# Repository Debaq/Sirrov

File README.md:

<hr>

Simulador interactivo de respuesta reflejo ovulo vestibular

Sirrov es un simulador del movimiento ocular y la respuesta vestibular frente a pruebas caloricas, movimientos rotacionales. El hardware esta basado en raspberri py pero es perfectamente utilizable en otras plataformas que admitan python, sdl, y la posibilidad de conectar dos pantallas spi, a continuación una descripción del equipo en cuestión:

Estructura del proyecto:
- Software [Software]
    - Sirrov 
    - Sirrov-ctrl
- Hardware [Hardware]
    - Eye Pi [eye-pi]
    - Eye Pressure [ ]
    - Ear Sensor [ ]
    - Neck Sensor [ ]
    - Power Supply [ ]
- Documentación [doc](doc/)
    - Imagenes usadas [img]

# Colaboradores
- Escuela de Tecnología Médica Universidad Austral de Chile (http://tmedicapm.uach.cl/)
- TM. Eliezer Lillo Oyarzo  (https://cl.linkedin.com/in/eliezer-neftal%C3%AD-lillo-oyarzo-90810089)

*Sirrov, es un proyecto creado por Nicolás Quezada Baier*

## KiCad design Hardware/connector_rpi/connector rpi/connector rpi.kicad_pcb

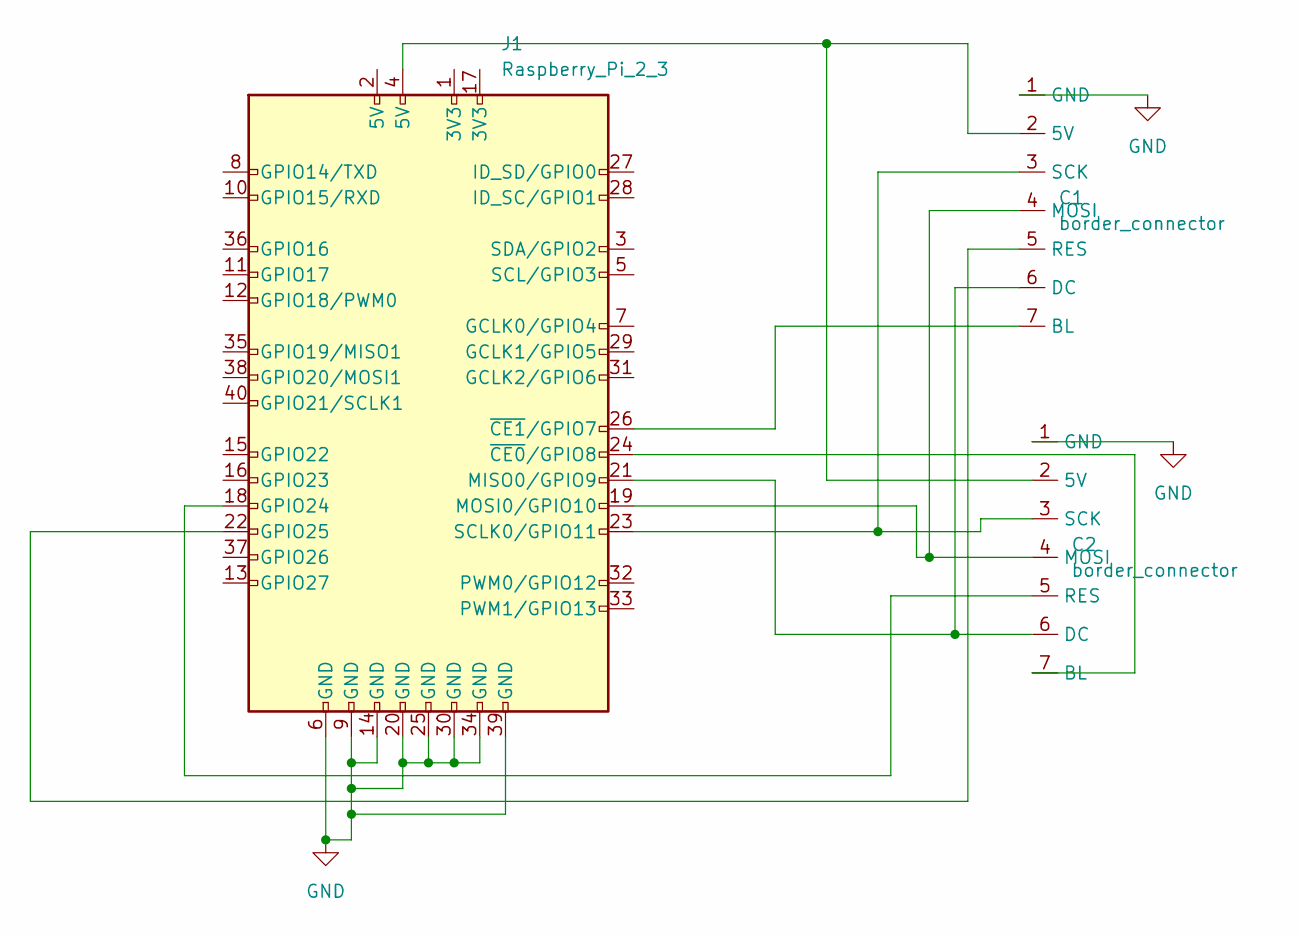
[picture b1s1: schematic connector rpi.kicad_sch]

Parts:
C1, C2: border_connector; connector placa st7789
J1: Raspberry_Pi_2_3; PinSocket_2x20_P2.54mm_Vertical

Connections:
GND: C1.1 (GND), C2.1 (GND), J1.6 (GND), J1.9 (GND), J1.14 (GND), J1.20 (GND), J1.25 (GND), J1.30 (GND), J1.34 (GND), J1.39 (GND)
unnamed: C1.2 (5V), C2.2 (5V), J1.4 (5V)
unnamed: C1.3 (SCK), C2.3 (SCK), J1.23 (SCLK0/GPIO11)
unnamed: C1.4 (MOSI), C2.4 (MOSI), J1.19 (MOSI0/GPIO10)
unnamed: C1.5 (RES), J1.22 (GPIO25)
unnamed: C1.6 (DC), C2.6 (DC), J1.21 (MISO0/GPIO9)
unnamed: C1.7 (BL), J1.26 (~CE1/GPIO7)
unnamed: C2.5 (RES), J1.18 (GPIO24)
unnamed: C2.7 (BL), J1.24 (~CE0/GPIO8)

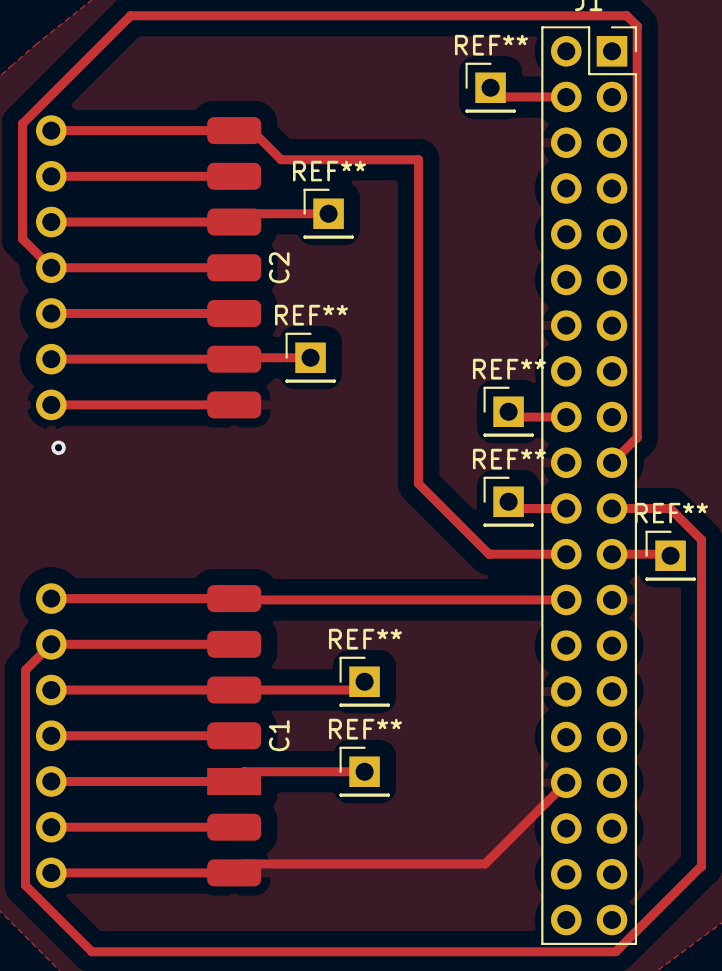
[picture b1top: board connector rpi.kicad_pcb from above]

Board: 2 copper layers, 3 parts (0 on the bottom side), 9 nets.

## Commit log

2021-12-30 creando logo
2021-12-30 javasript
2021-12-30 se eliminan alchivos sin uso
2022-07-31 cambios de inicio
2022-08-15 'Refactored by Sourcery'
